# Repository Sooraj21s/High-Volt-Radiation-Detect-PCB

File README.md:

# High-Volt-Radiation-Detect-PCB
A PCB that converts the radiatoin detected by the geiger tube captured as milli volts to a high voltage by opamp &amp; a buzzer is also provided in the module that triggers when the detected voltage reaches a certain threshold.

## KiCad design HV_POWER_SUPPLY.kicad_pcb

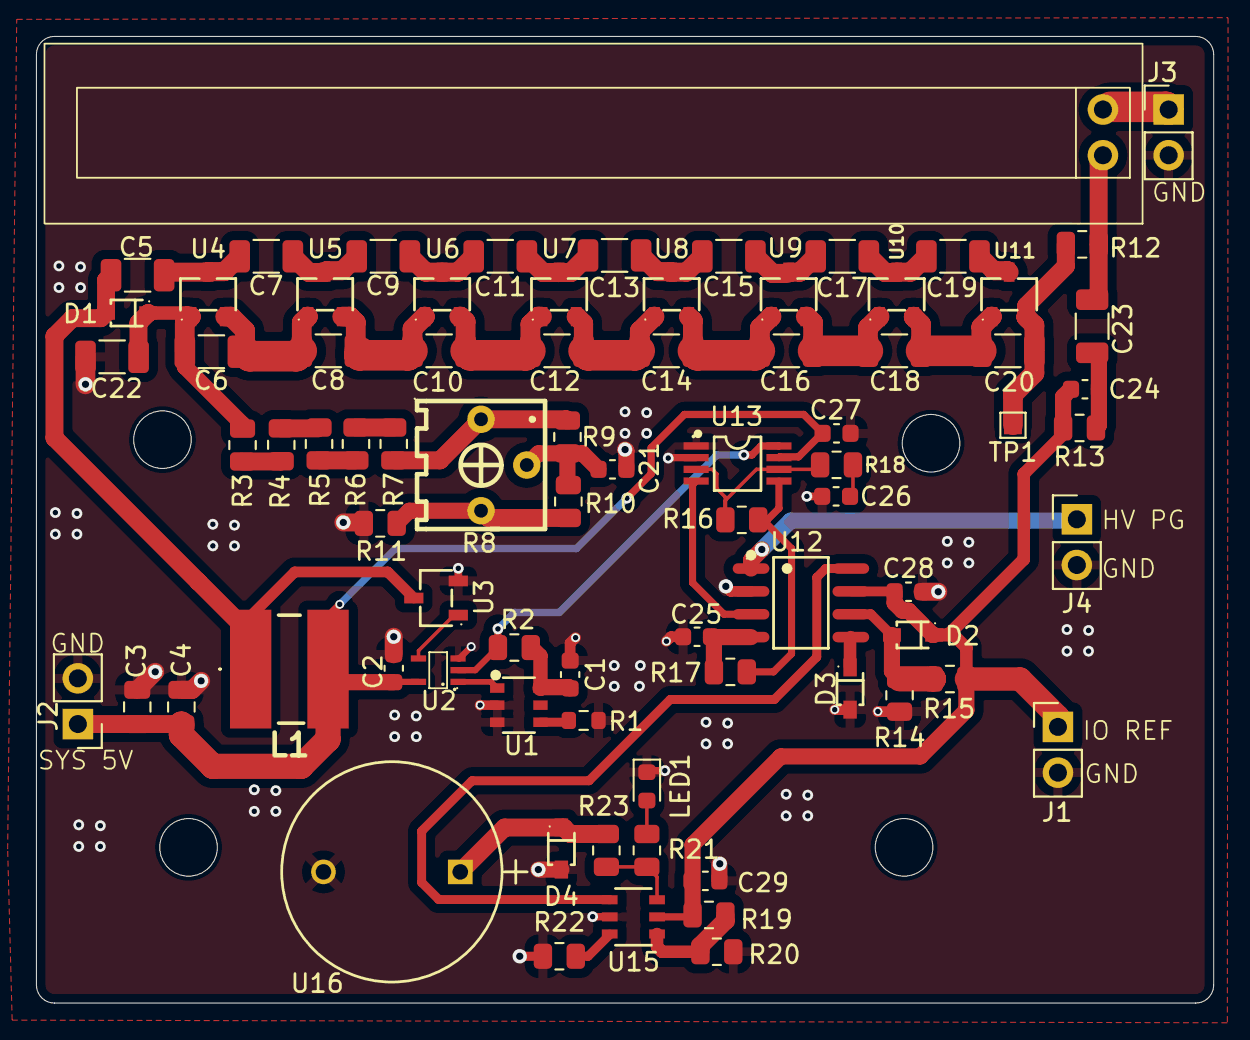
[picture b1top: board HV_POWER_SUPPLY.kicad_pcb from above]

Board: 4 copper layers, 65.4 x 53.7 mm, 83 parts (0 on the bottom side), 50 nets.

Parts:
C1, C2, C26, C27, C28, C29: 1uF; C_0603_1608Metric
C3, C4: 10uF; C_0805_2012Metric
C5, C6, C7, C8, C9, C10, C11, C12, C13, C14, C15, C16, C17, C18, C19, C20, C22: 0.1uF; C_1206_3216Metric
C21, C25: 47pF; C_0603_1608Metric
C23: 10pF; C_1206_3216Metric
C24: 250pF; C_0603_1608Metric
D1, D2, D3: BAV21W-7-F; SOD-323_L1.8-W1.3-LS2.5-RD
D4: BAS16HT1G; SOD-323_L1.8-W1.3-LS2.5-RD
H1, H2, H3, H4: MountingHole; MountingHole_3.2mm_M3
J1, J2, J3, J4: Conn_01x02; PinHeader_1x02_P2.54mm_Vertical
L1: LPS6235-473MRB; LPS6235473MRB
LED1: TLMS1000-GS08; LED_0603_1608Metric
R1: 287K; R_0603_1608Metric
R2: 221; R_0805_2012Metric
R3, R4, R5: 30Meg; R_0805_2012Metric
R6: 7.5Meg; R_0805_2012Metric
R7, R14: 3Meg; R_0805_2012Metric
R8: 3362P-1-205LF; RES-ADJ-TH_3362P
R9, R10: 1Meg; R_0805_2012Metric
R11: 2.7Meg; R_0805_2012Metric
R12: 7.5 Meg; R_0805_2012Metric
R13: 200K; R_0805_2012Metric
R15: 2Meg; R_0805_2012Metric
R16, R19, R22: 127K; R_0805_2012Metric
R17, R20: 453K; R_0805_2012Metric
R18: 1K; R_0805_2012Metric
R21: 330; R_0805_2012Metric
R23: 100; R_0805_2012Metric
TP1: TestPoint; TestPoint_Pad_1.0x1.0mm
U1: LTC6906IS6#TRPBF; TSOT-23-6_L2.9-W1.6-P0.95-LS2.8-BR
U2: SN74LVC1G08DCKR_C5279048; SC-70-5_L2.0-W1.3-P0.65-LS2.1-BR
U3: DMN10H220L-7; SOT-23-3_L2.9-W1.6-P1.90-LS2.8-BR
U4, U5, U6, U7, U8, U9, U10, U11: BAV23S; BAV23S_SOT-23-3_L2.9-W1.6-P1.90-LS2.8-BR
U12: LTC1441CS8#PBF; SOIC-8_L4.9-W3.8-P1.27-LS6.0-BL
U13: LTC1540IMS8#PBF; MSOP-8_L3.0-W3.0-P0.65-LS4.9-BL
U14: SI-29BG
U15: LTC6994CS6-1-TRMPBF; TSOT-23_S6_LIT
U16: AI-1223-TWT-5V-5-R; AI-1223-TWT-5V-5-R_PUI

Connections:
/GEIGER_DETECTB: C23.2, C24.1, R13.1
/POT_METER: C21.1, R8.2, R9.2, R10.1
/Page 2/DETECT_OUTPUT: U12.8 (OUT), U15.1 (IN)
/Page 2/GEIGER_DETECTB: D3.1, U12.5 (IN-)
/Page 2/HV_PG: J4.1, U12.1 (OUT)
/Page 2/POT_METER: U12.3 (IN+), U13.4 (IN-)
/SW_NODE: C5.1, D1.2, L1.1, U3.3 (D)
BOOST_EN: R2.2, U2.2 (B), U13.8 (OUT)
GND: C1.2, C2.2, C3.2, C4.2, C21.2, C22.2, C25.2, C26.2, C27.2, C28.2, C29.2, D3.2, D4.2 (A), J1.2, J2.2, J3.2, J4.2, LED1.1, R1.2, R11.2, R14.2, R20.2, R22.2, U1.2 (GND), U1.3 (DIV), U2.3 (GND), U3.2 (S), U12.2 (V-), U13.1 (GND), U13.2 (V-), U15.2 (GND), U16.2
IO_VREF: C24.2, C28.1, C29.1, D2.1, J1.1, R13.2, R15.1, R19.1, U12.7 (V+), U15.5 (V+)
unnamed: C5.2, C7.1, U4.3
unnamed: C6.2, C8.1, U4.2, U5.1
unnamed: C7.2, C9.1, U5.3
unnamed: C8.2, C10.1, U5.2, U6.1
unnamed: C10.2, C12.1, U6.2, U7.1
unnamed: C9.2, C11.1, U6.3
unnamed: C11.2, C13.1, U7.3
unnamed: C12.2, C14.1, U7.2, U8.1
unnamed: C13.2, C15.1, U8.3
unnamed: C14.2, C16.1, U8.2, U9.1
unnamed: C15.2, C17.1, U9.3
unnamed: C16.2, C18.1, U9.2, U10.1
unnamed: C17.2, C19.1, U10.3
unnamed: C18.2, C20.1, U10.2, U11.1
unnamed: C19.2, U11.3
unnamed: C20.2, R12.1, TP1.1, U11.2
unnamed: C6.1, C22.1, D1.1, R3.1, U4.1
unnamed: C26.1, R18.2
unnamed: D4.1 (C), R23.2, U16.1
unnamed: J3.1, U14.2
unnamed: LED1.2, R21.2
unnamed: R3.2, R4.1
unnamed: R4.2, R5.1
unnamed: R5.2, R6.1
unnamed: R6.2, R7.1
unnamed: R7.2, R8.1, R9.1
unnamed: R8.3, R10.2, R11.1
unnamed: U1.1 (OUT), U2.1 (A)
unnamed: R1.1, U1.4 (SET)
unnamed: C1.1, R2.1, U1.6 (V+)
unnamed: U2.4 (Y), U3.1 (G)
unnamed: C25.1, R17.2, U12.4 (IN-)
unnamed: D2.2, R14.1, R15.2, U12.6 (IN+)
unnamed: R16.2, R17.1, U13.5 (HYST)
unnamed: R16.1, R18.1, U13.3 (IN+), U13.6 (REF)
unnamed: C23.1, R12.2, U14.1 (+)
unnamed: R19.2, R20.1, U15.4 (DIV)
unnamed: R21.1, R23.1, U15.6 (OUT)
unnamed: R22.1, U15.3 (SET)
SYS_5V: C2.1, C3.1, C4.1, C27.1, J2.1, L1.2, U2.5 (VCC), U13.7 (V+)

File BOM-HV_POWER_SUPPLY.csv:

Comment,Designator,Footprint,LCSC
1K,R18,R_0805_2012Metric,C100046
DMN10H220L-7,U3,SOT-23-3_L2.9-W1.6-P1.90-LS2.8-BR,C102615
1Meg,"R10,R9",R_0805_2012Metric,C107700
3362P-1-205LF,R8,RES-ADJ-TH_3362P,C124582
BAS16HT1G,D4,SOD-323_L1.8-W1.3-LS2.5-RD,C131148
BAV21W-7-F,"D1,D2,D3",SOD-323_L1.8-W1.3-LS2.5-RD,C151350
1uF,"C1,C2,C26,C27,C28,C29",C_0603_1608Metric,C15849
10uF,"C3,C4",C_0805_2012Metric,C15850
100,R23,R_0805_2012Metric,C17408
200K,R13,R_0805_2012Metric,C17539
330,R21,R_0805_2012Metric,C17630
453K,"R17,R20",R_0805_2012Metric,C17702
47pF,"C21,C25",C_0603_1608Metric,C178330
221,R2,R_0805_2012Metric,C204308
127K,"R16,R19,R22",R_0805_2012Metric,C228282
TLMS1000-GS08,LED1,LED_0603_1608Metric,C2286
287K,R1,R_0603_1608Metric,C22972
0.1uF,"C10,C11,C12,C13,C14,C15,C16,C17,C18,C19,C20,C22,C5,C6,C7,C8,C9",C_1206_3216Metric,C24497
2Meg,R15,R_0805_2012Metric,C26112
3Meg,"R14,R7",R_0805_2012Metric,C2907325
2.7Meg,R11,R_0805_2012Metric,C2933390
7.5 Meg,"R12,R6",R_0805_2012Metric,C2933569
30Meg,"R3,R4,R5",R_0805_2012Metric,C317991
10pF,C23,C_1206_3216Metric,C377014
BAV23S,"U10,U11,U4,U5,U6,U7,U8,U9",BAV23S_SOT-23-3_L2.9-W1.6-P1.90-LS2.8-BR,C44345
AI-1223-TWT-5V-5-R,U16,AI-1223-TWT-5V-5-R_PUI,C5250722
SN74LVC1G08DCKR_C5279048,U2,SC-70-5_L2.0-W1.3-P0.65-LS2.1-BR,C5279048
LTC1540IMS8#PBF,U13,MSOP-8_L3.0-W3.0-P0.65-LS4.9-BL,C580397
LTC6994CS6-1-TRMPBF,U15,TSOT-23_S6_LIT,C581050
LTC1441CS8#PBF,U12,SOIC-8_L4.9-W3.8-P1.27-LS6.0-BL,C675522
LTC6906IS6#TRPBF,U1,TSOT-23-6_L2.9-W1.6-P0.95-LS2.8-BR,C689638
Conn_01x02,J1,PinHeader_1x02_P2.54mm_Vertical,
SI-29BG,U14,SI-29BG,
Conn_01x02,J3,PinHeader_1x02_P2.54mm_Vertical,
LPS6235-473MRB,L1,LPS6235473MRB,
250pF,C24,C_0603_1608Metric,
Conn_01x02,J4,PinHeader_1x02_P2.54mm_Vertical,
TestPoint,TP1,TestPoint_Pad_1.0x1.0mm,
Conn_01x02,J2,PinHeader_1x02_P2.54mm_Vertical,
